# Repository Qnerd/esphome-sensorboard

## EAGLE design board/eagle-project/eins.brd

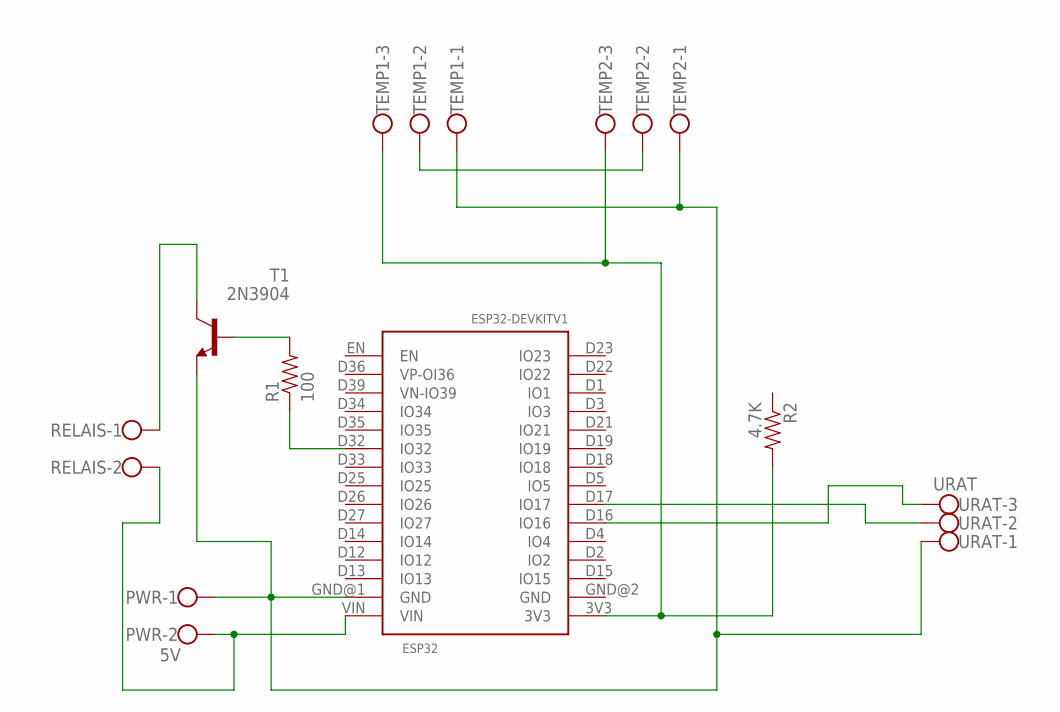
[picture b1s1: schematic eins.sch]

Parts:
ESP32: ESP32DEVKITV1; ESP32-DEVKITV1
PWR: 5V; W237-102
R1: 100; AXIAL-0.4
R2: 4.7K; AXIAL-0.4
RELAIS: W237-102
T1: 2N3904; TO92
TEMP1, TEMP2: W237-103
URAT: URAT; W237-103

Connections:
GND: ESP32.GND@1 (GND), PWR.1, T1.3 (E), TEMP1.1, TEMP2.1, URAT.1
unnamed: ESP32.D17 (IO17), URAT.2
unnamed: ESP32.VIN, PWR.2, RELAIS.2
unnamed: R1.P$2 (2), T1.2 (B)
unnamed: RELAIS.1, T1.1 (C)
unnamed: ESP32.D32 (IO32), R1.P$1 (1)
unnamed: ESP32.3V3, R2.P$2 (2), TEMP1.3, TEMP2.3
unnamed: ESP32.D18 (IO18), R2.P$1 (1), TEMP1.2, TEMP2.2
unnamed: ESP32.D16 (IO16), URAT.3

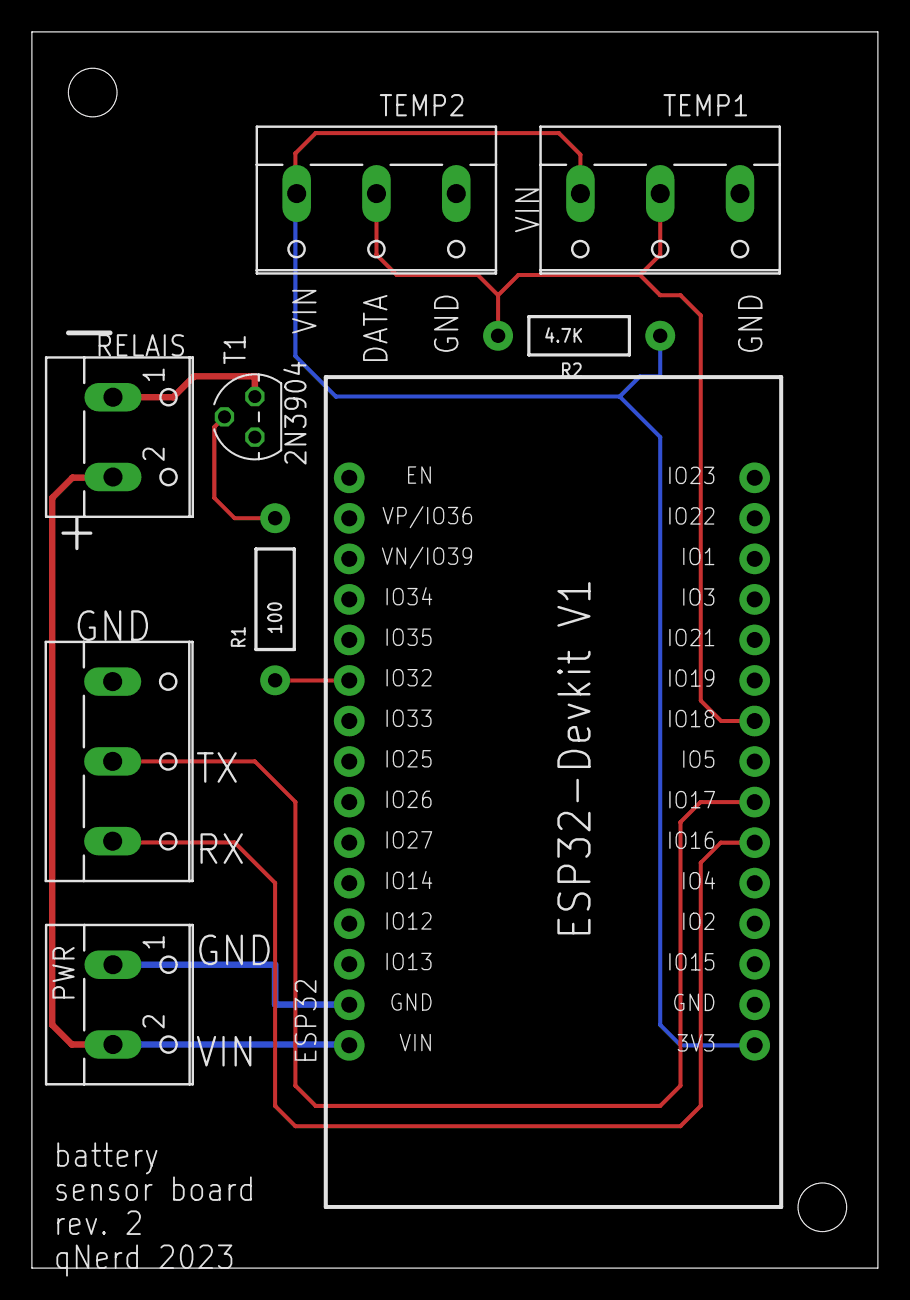
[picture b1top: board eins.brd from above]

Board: 2 copper layers, 53.0 x 77.5 mm, 9 parts (0 on the bottom side), 9 nets.

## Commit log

2023-04-15 readme modified
2023-04-16 fallback wifi ap

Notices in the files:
parts and their libraries:
SparkFun-Passives: Licensing: Creative Commons ShareAlike 4.0 International - https://creativecommons.org/licenses/by-sa/4.0
